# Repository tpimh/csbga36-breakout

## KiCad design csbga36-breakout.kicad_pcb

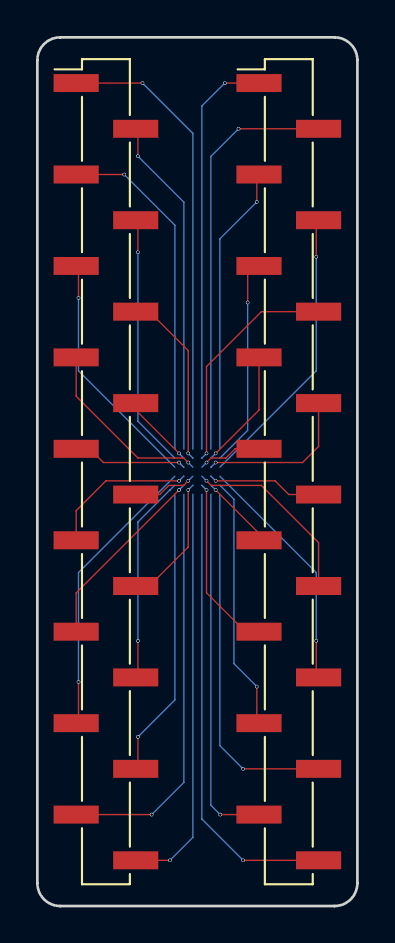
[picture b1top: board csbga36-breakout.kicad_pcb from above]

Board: 2 copper layers, 17.8 x 48.3 mm, 3 parts (1 on the bottom side), 36 nets.

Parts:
J1, J2: Conn_01x18_Male; PinHeader_1x18_P2.54mm_Vertical_SMD_Pin1Left
csBGA-36: BGA-36_6x6; CSBGA-36_4x4mm_Layout6x6_P0.5mm

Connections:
/A1: J1.3, csBGA-36.A1
/A2: J1.2, csBGA-36.A2
/A3: J1.1, csBGA-36.A3
/A4: J2.1, csBGA-36.A4
/A5: J2.2, csBGA-36.A5
/A6: J2.3, csBGA-36.A6
/B1: J1.5, csBGA-36.B1
/B2: J1.7, csBGA-36.B2
/B3: J1.6, csBGA-36.B3
/B4: J2.6, csBGA-36.B4
/B5: J2.8, csBGA-36.B5
/B6: J2.4, csBGA-36.B6
/C1: J1.4, csBGA-36.C1
/C2: J1.8, csBGA-36.C2
/C3: J1.9, csBGA-36.C3
/C4: J2.7, csBGA-36.C4
/C5: J2.9, csBGA-36.C5
/C6: J2.5, csBGA-36.C6
/D1: J1.14, csBGA-36.D1
/D2: J1.10, csBGA-36.D2
/D3: J1.12, csBGA-36.D3
/D4: J2.10, csBGA-36.D4
/D5: J2.11, csBGA-36.D5
/D6: J2.15, csBGA-36.D6
/E1: J1.15, csBGA-36.E1
/E2: J1.11, csBGA-36.E2
/E3: J1.13, csBGA-36.E3
/E4: J2.12, csBGA-36.E4
/E5: J2.13, csBGA-36.E5
/E6: J2.14, csBGA-36.E6
/F1: J1.16, csBGA-36.F1
/F2: J1.17, csBGA-36.F2
/F3: J1.18, csBGA-36.F3
/F4: J2.18, csBGA-36.F4
/F5: J2.17, csBGA-36.F5
/F6: J2.16, csBGA-36.F6

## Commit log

2018-08-08 Yay! First commit!
2018-08-09 naming all nets, adding informational text
2018-12-15 move vias away from bga pads
2021-04-30 Change /Users/superapp070318/Documents/KiCAD/csbga36-breakout to ${KIPRJMOD}
